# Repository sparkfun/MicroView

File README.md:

MicroView
=============

[*SparkFun Microview (DEV-12923)*](https://www.sparkfun.com/products/12923)

The MicroView is a chip-sized Arduino with a built-in OLED. Compatible with the MicroView USB Programmer linked below. 

Repository Contents
-------------------
* **/Datasheets** - Datasheets for the OLED module
* **/Enclosure** - 3D model of the standard Microview Enclosure
* **/Hardware** - All Eagle design files (.brd, .sch)
* **/Libraries** - All Arduino libraries and board examples
* **/Production** - Test bed files and production panel files

Product Versions
----------------
* [DEV-12923](https://www.sparkfun.com/products/12923)- Version 1.0
* [DEV-12924](https://www.sparkfun.com/products/12924)- MicroView USB Programmer version 0.2

License Information
-------------------
The hardware is released under [Creative Commons ShareAlike 4.0 International](https://creativecommons.org/licenses/by-sa/4.0/).
The code is beerware; if you see me (or any other SparkFun employee) at the local, and you've found our code helpful, please buy us a round!

Distributed as-is; no warranty is given.

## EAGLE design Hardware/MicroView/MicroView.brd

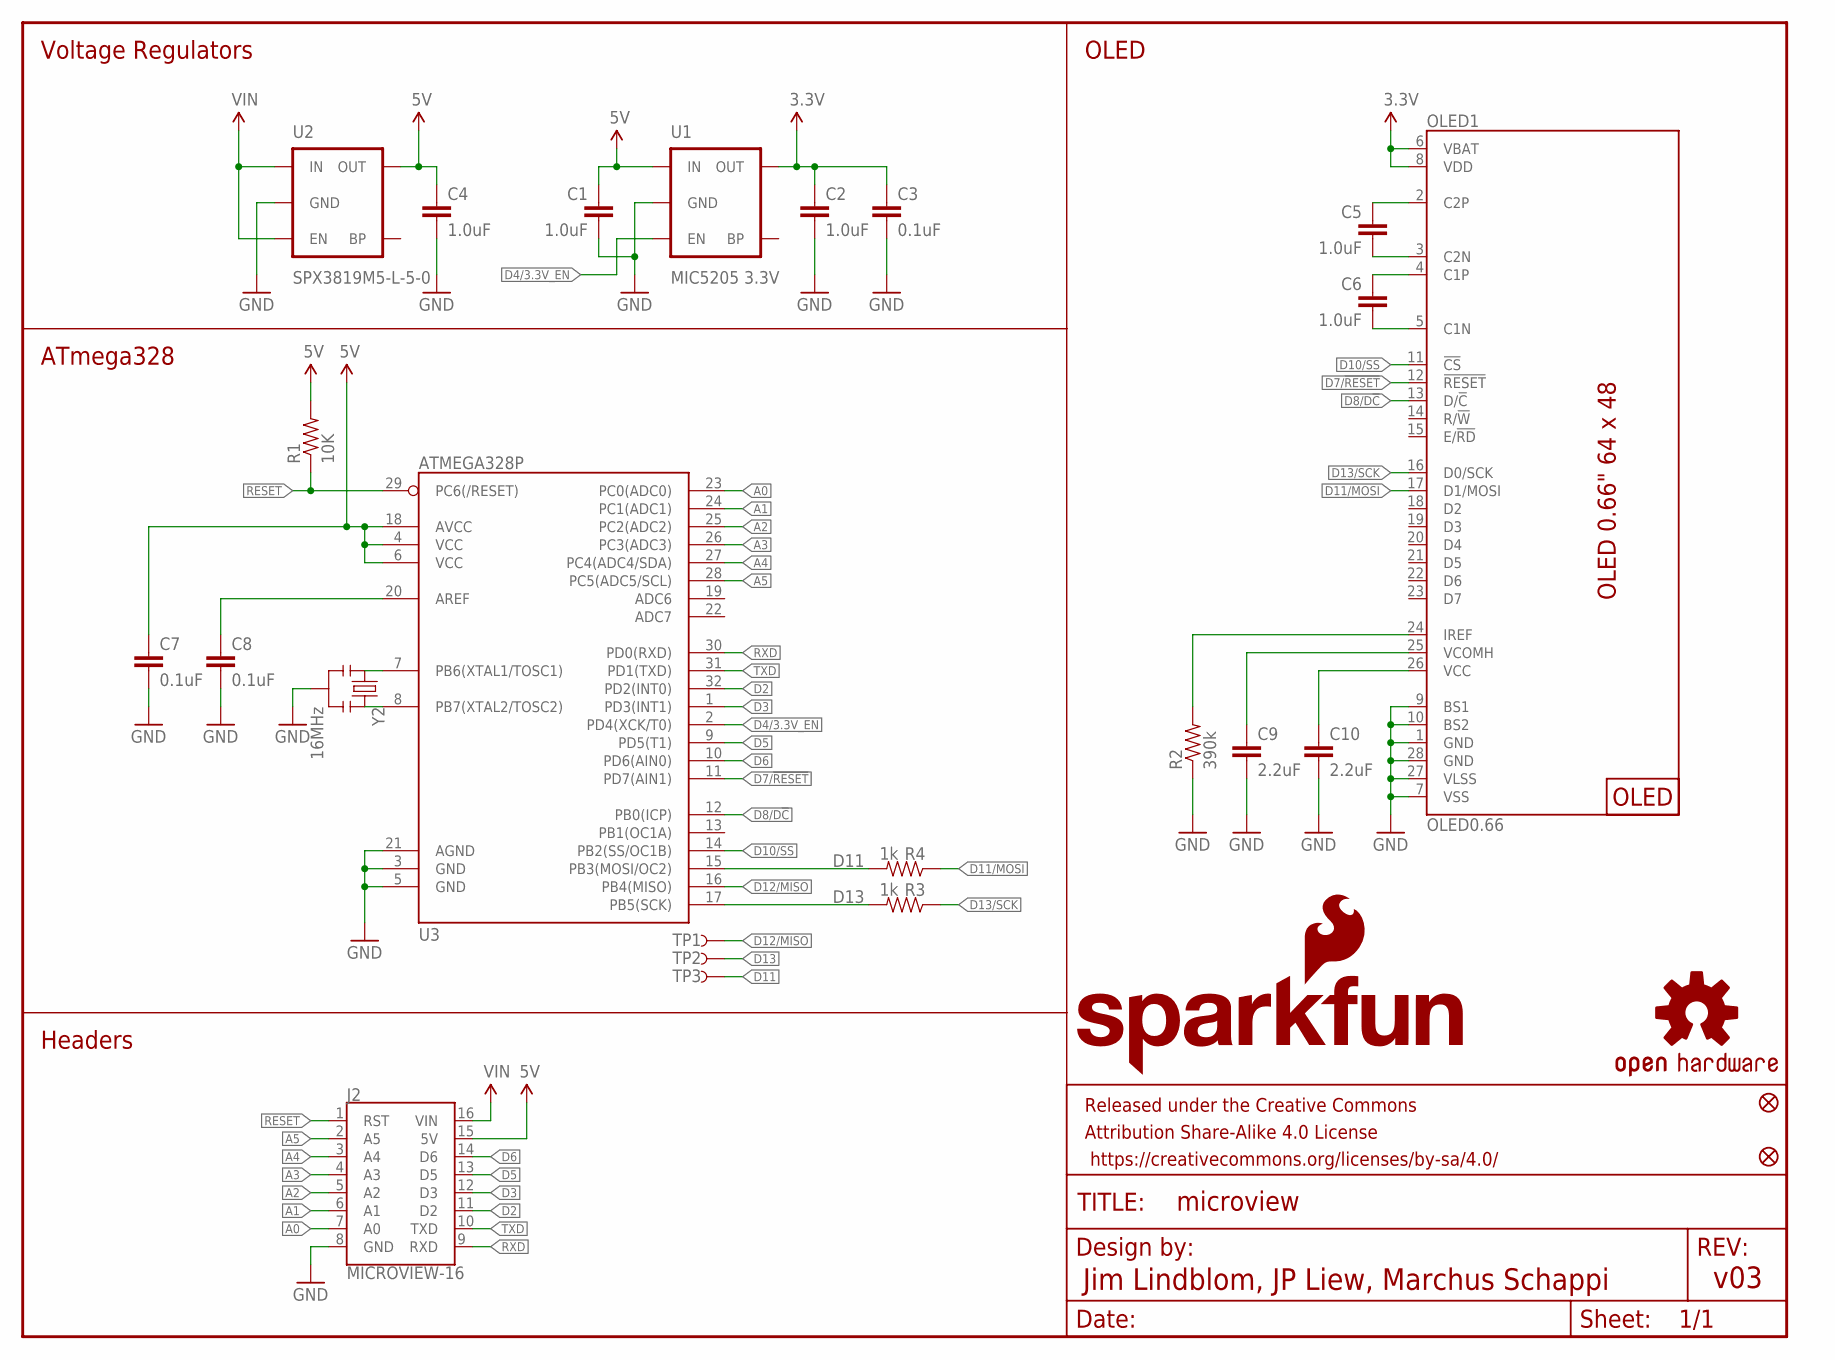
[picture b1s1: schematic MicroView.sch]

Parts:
C1, C2, C4, C5, C6: 1.0uF; 0603-CAP
C3, C7, C8: 0.1uF; 0603-CAP
C9, C10: 2.2uF; 0603-CAP
FID1, FID3: FIDUCIALUFIDUCIAL; MICRO-FIDUCIAL
FRAME1: FRAME-LETTER; CREATIVE_COMMONS
J1: OLED_SCREEN; OLED-SCREEN
J2: MICROVIEW-16; MV-DIP16
LOGO1: OSHW-LOGOS; OSHW-LOGO-S
LOGO4: SFE_LOGO_NAME_FLAME.1_INCH; SFE_LOGO_NAME_FLAME_.1
OLED1: OLED0.66; OLED-0.66-64X48
R1: 10K; 0603-RES
R2: 390k; 0603-RES
R3, R4: 1k; 0603-RES
TP1, TP2, TP3: TEST-POINT3X5; PAD.03X.05
U1: MIC5205 3.3V; SOT23-5
U2: SPX3819M5-L-5-0; SOT23-5
U3: ATMEGA328P; TQFP32-08
Y2: 16MHz; RESONATOR-SMD

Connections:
3.3V: C2.1, C3.1, OLED1.6 (VBAT), OLED1.8 (VDD), U1.5 (OUT)
5V: C1.1, C4.1, C7.1, J2.15 (5V), R1.2, U1.1 (IN), U2.5 (OUT), U3.4 (VCC), U3.6 (VCC), U3.18 (AVCC)
A0: J2.7 (A0), U3.23 (PC0(ADC0))
A1: J2.6 (A1), U3.24 (PC1(ADC1))
A2: J2.5 (A2), U3.25 (PC2(ADC2))
A3: J2.4 (A3), U3.26 (PC3(ADC3))
A4: J2.3 (A4), U3.27 (PC4(ADC4/SDA))
A5: J2.2 (A5), U3.28 (PC5(ADC5/SCL))
C1N: C6.2, OLED1.5 (C1N)
C1P: C6.1, OLED1.4 (C1P)
C2N: C5.2, OLED1.3 (C2N)
C2P: C5.1, OLED1.2 (C2P)
D2: J2.11 (D2), U3.32 (PD2(INT0))
D3: J2.12 (D3), U3.1 (PD3(INT1))
D4/3.3V_EN: U1.3 (EN), U3.2 (PD4(XCK/T0))
D5: J2.13 (D5), U3.9 (PD5(T1))
D6: J2.14 (D6), U3.10 (PD6(AIN0))
D7/!RESET!: OLED1.12 (!RESET!), U3.11 (PD7(AIN1))
D8/D!C!: OLED1.13 (D/!C!), U3.12 (PB0(ICP))
D10/SS: OLED1.11 (!CS!), U3.14 (PB2(SS/OC1B))
D11: R4.2, TP3.P$1, U3.15 (PB3(MOSI/OC2))
D11/MOSI: OLED1.17 (D1/MOSI), R4.1
D12/MISO: TP1.P$1, U3.16 (PB4(MISO))
D13: R3.2, TP2.P$1, U3.17 (PB5(SCK))
D13/SCK: OLED1.16 (D0/SCK), R3.1
GND: C1.2, C2.2, C3.2, C4.2, C7.2, C8.2, C9.2, C10.2, J2.8 (GND), OLED1.1 (GND), OLED1.7 (VSS), OLED1.9 (BS1), OLED1.10 (BS2), OLED1.27 (VLSS), OLED1.28 (GND), R2.1, U1.2 (GND), U2.2 (GND), U3.3 (GND), U3.5 (GND), U3.21 (AGND), Y2.2
unnamed: C10.1, OLED1.26 (VCC)
unnamed: C9.1, OLED1.25 (VCOMH)
unnamed: OLED1.24 (IREF), R2.2
unnamed: U3.7 (PB6(XTAL1/TOSC1)), Y2.1
unnamed: U3.8 (PB7(XTAL2/TOSC2)), Y2.3
unnamed: C8.1, U3.20 (AREF)
RESET: J2.1 (RST), R1.1, U3.29 (PC6(/RESET))
RXD: J2.9 (RXD), U3.30 (PD0(RXD))
TXD: J2.10 (TXD), U3.31 (PD1(TXD))
VIN: J2.16 (VIN), U2.1 (IN), U2.3 (EN)

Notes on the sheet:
v03
Jim Lindblom, JP Liew, Marchus Schappi
Voltage Regulators
ATmega328
OLED
Headers

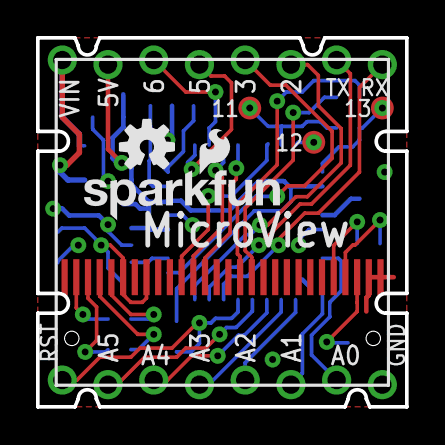
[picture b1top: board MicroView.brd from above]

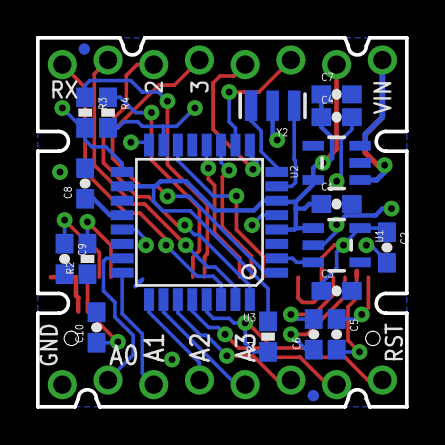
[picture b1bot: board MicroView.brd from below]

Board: 2 copper layers, 20.5 x 20.5 mm, 29 parts (20 on the bottom side), 36 nets.

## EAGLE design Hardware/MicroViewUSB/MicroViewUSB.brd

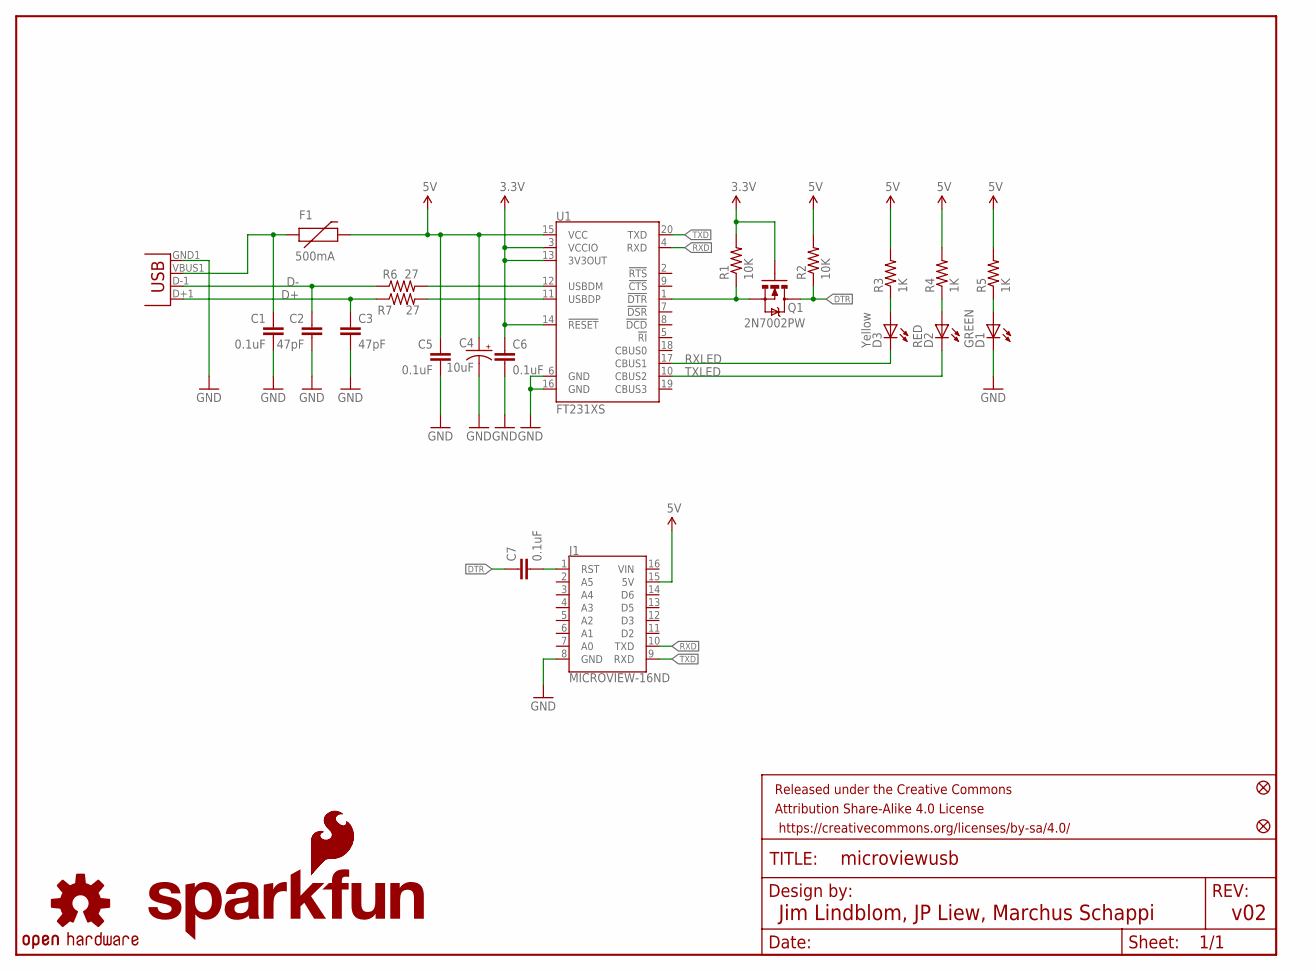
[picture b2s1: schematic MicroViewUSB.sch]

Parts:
C1, C5, C6, C7: 0.1uF; 0603-CAP
C2, C3: 47pF; 0603-CAP
C4: 10uF; EIA3216
D1: GREEN; LED-1206
D2: RED; LED-1206
D3: Yellow; LED-1206
F1: 500mA; PTC-1206-WIDE
FID1, FID2: FIDUCIAL1X2; FIDUCIAL-1X2
FRAME1: FRAME-LETTER; CREATIVE_COMMONS
J1: MICROVIEW-16ND; MV-DIP16-NODIMENSION
JP1: USBA-SMD-MALE; USB-A-SMT-MALE
LOGO1: SFE_LOGO_FLAME.1_INCH; SFE_LOGO_FLAME_.1
LOGO2: OSHW-LOGOS; OSHW-LOGO-S
LOGO3: SFE_LOGO_NAME_FLAME.1_INCH; SFE_LOGO_NAME_FLAME_.1
Q1: 2N7002PW; SOT323
R1, R2: 10K; 0603-RES
R3, R4, R5: 1K; 0603-RES
R6, R7: 27; 0603-RES
U1: FT231XS; SSOP20_L

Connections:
3.3V: C6.1, Q1.1 (G), R1.2, U1.3 (VCCIO), U1.13 (3V3OUT), U1.14 (!RESET)
5V: C4.A (+), C5.1, F1.2, J1.15 (5V), R2.2, R3.2, R4.2, R5.2, U1.15 (VCC)
D+: C3.1, JP1.D+1 (D+), R7.1
D-: C2.1, JP1.D-1 (D-), R6.1
DTR: C7.1, Q1.3 (D), R2.1
GND: C1.2, C2.2, C3.2, C4.C (-), C5.2, C6.2, D1.C, J1.8 (GND), JP1.GND1 (GND), U1.6 (GND), U1.16 (GND)
unnamed: D1.A, R5.1
unnamed: C7.2, J1.1 (RST)
unnamed: R6.2, U1.12 (USBDM)
unnamed: R7.2, U1.11 (USBDP)
unnamed: D2.A, R4.1
unnamed: D3.A, R3.1
unnamed: Q1.2 (S), R1.1, U1.1 (!DTR)
RXD: J1.10 (TXD), U1.4 (RXD)
RXLED: D3.C, U1.17 (CBUS1)
TXD: J1.9 (RXD), U1.20 (TXD)
TXLED: D2.C, U1.10 (CBUS2)
VUSB: C1.1, F1.1, JP1.VBUS1 (VBUS)

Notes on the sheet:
v02
Jim Lindblom, JP Liew, Marchus Schappi

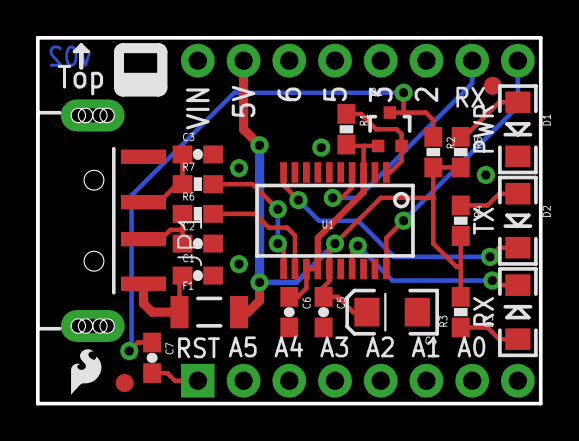
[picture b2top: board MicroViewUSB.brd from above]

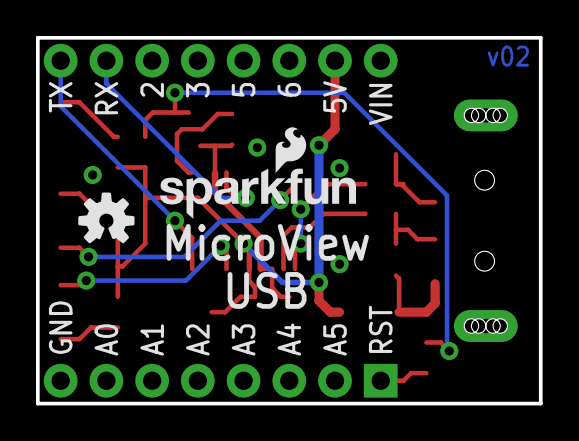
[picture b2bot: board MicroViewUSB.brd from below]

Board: 2 copper layers, 27.9 x 20.3 mm, 28 parts (2 on the bottom side), 18 nets.

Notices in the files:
parts and their libraries:
SparkFun-Aesthetics: Licensing: Creative Commons ShareAlike 4.0 International - https://creativecommons.org/licenses/by-sa/4.0
SparkFun-Aesthetics: Released under the Creative Commons Attribution Share-Alike 4.0 License
SparkFun-Aesthetics: Released under the Creative Commons
